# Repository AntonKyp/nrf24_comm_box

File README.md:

# nrf24_comm_box
A communication box which sends flight control commands to a quad copter

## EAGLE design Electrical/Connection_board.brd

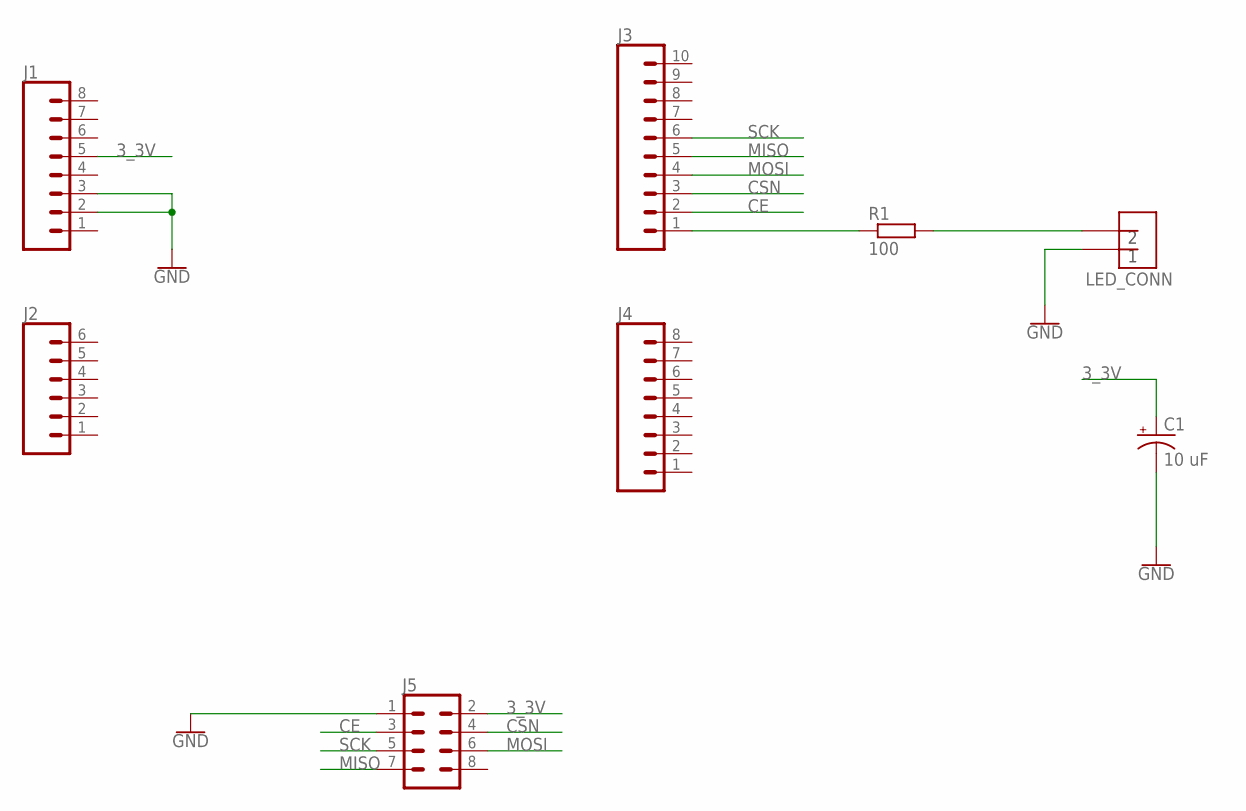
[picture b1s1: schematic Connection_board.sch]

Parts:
C1: 10 uF; E2-5
J1, J4: CONN_08"; 1X08
J2: CONN_06SILK_FEMALE_PTH; 1X06
J3: CONN_10"; 1X10
J5: CONN_04X2; 2X4
LED_CONN: JST_2
R1: 100; 0207/10

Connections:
3_3V: C1.+, J1.5, J5.2
CE: J3.2, J5.3
CSN: J3.3, J5.4
GND: C1.-, J1.2, J1.3, J5.1, LED_CONN.P$1
MISO: J3.5, J5.7
MOSI: J3.4, J5.6
unnamed: LED_CONN.P$2, R1.2
unnamed: J3.1, R1.1
SCK: J3.6, J5.5

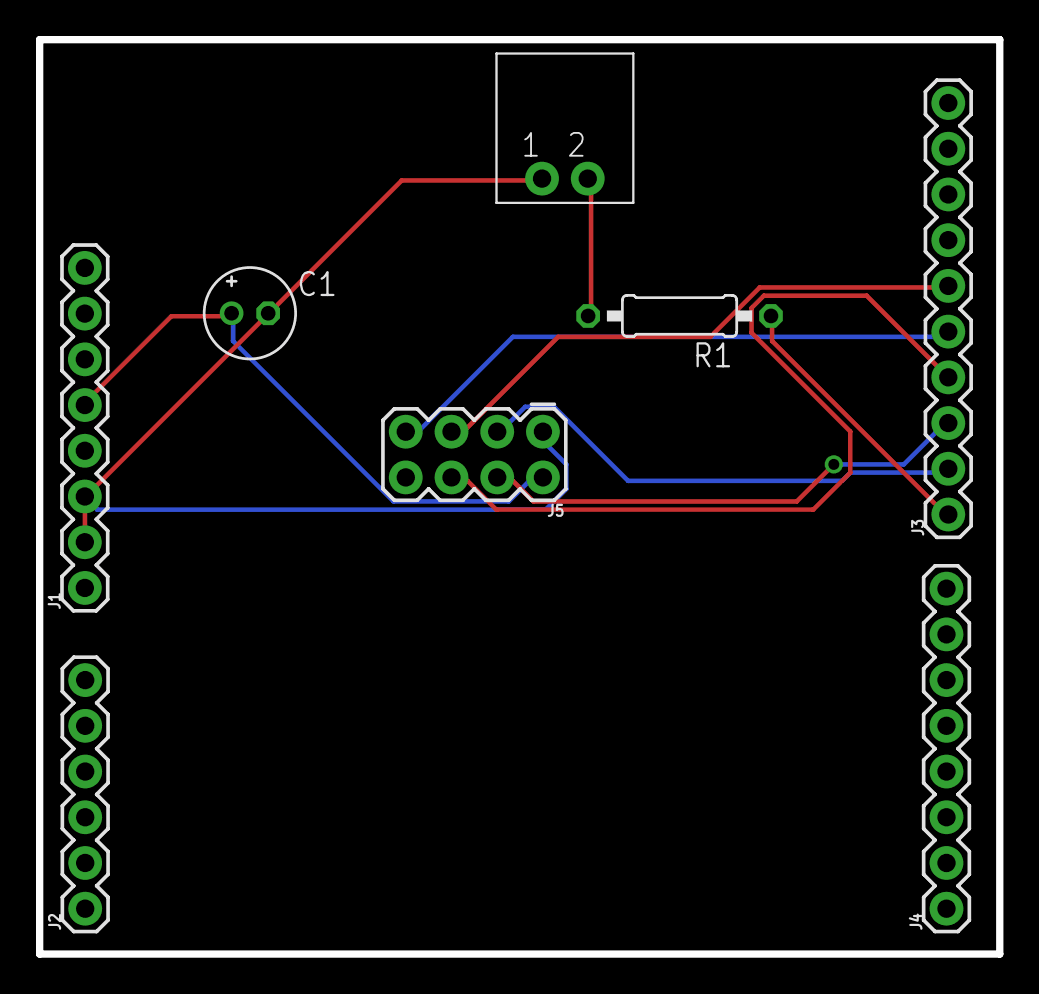
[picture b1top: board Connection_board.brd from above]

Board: 2 copper layers, 53.3 x 50.8 mm, 8 parts (0 on the bottom side), 9 nets.

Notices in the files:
parts and their libraries:
SparkFun-Connectors: Licensing: Creative Commons ShareAlike 4.0 International - https://creativecommons.org/licenses/by-sa/4.0
